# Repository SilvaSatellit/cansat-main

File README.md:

# Team Silva-Satellit

## Informationen

In diesem Respository ist der Sourcecode des Haupt-Mikrocontrollers, der im CanSat verbaut ist, zu finden. Dieser Controller ist für das Auslesen der Temperatur, Luftdruck, Luftfeutigkeit und Gyrodaten verantwortlich.

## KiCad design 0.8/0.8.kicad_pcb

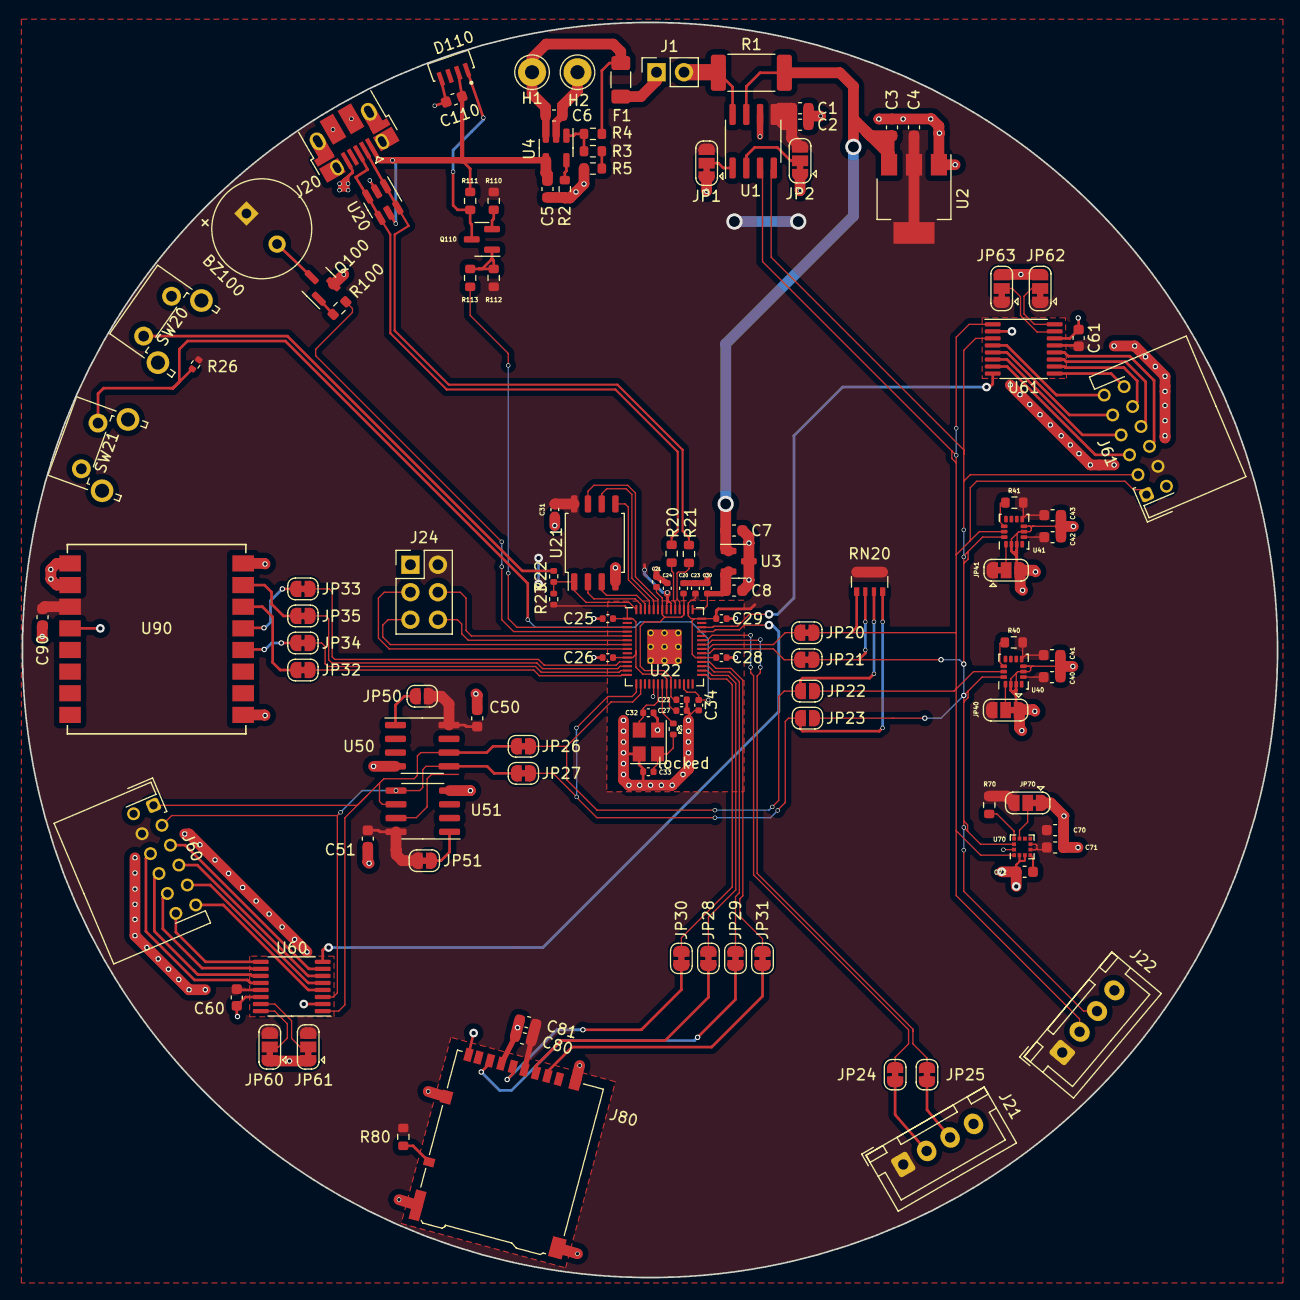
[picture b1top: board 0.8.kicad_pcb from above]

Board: 2 copper layers, 116.0 x 116.0 mm, 119 parts (0 on the bottom side), 98 nets.

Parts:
BZ100: CST-931RP-A; MagneticBuzzer_CUI_CST-931RP-A
C1, C40, C41, C42, C43, C50, C51, C60, C61, C71, C72, C80, C110: 100nF; C_0603_1608Metric
C2: 10uF; C_0603_1608Metric
C3, C70, C81: 1uF; C_0603_1608Metric
C4: 4,7uF; C_0603_1608Metric
C5, C6: 4,7 uF; C_0603_1608Metric
C7: 470nF; C_0603_1608Metric
C8: 10uF => Optional; C_0603_1608Metric
C20, C23, C34: 1uF; C_0402_1005Metric
C21, C22, C24, C25, C26, C27, C28, C29, C30, C31: 100nF; C_0402_1005Metric
C32, C33: 30pF; C_0402_1005Metric
C90: DNP; C_0603_1608Metric
D110: WS2812B-4020; LED_WS2812B-4020
F1: 1.5A; R_1206_3216Metric_Pad1.30x1.75mm_HandSolder
H1: Bat+; Pin_D1.3mm_L11.0mm
H2: Bat-; Pin_D1.3mm_L11.0mm
J1: Switch; PinSocket_1x02_P2.54mm_Vertical
J20: USB_B_Micro; USB_Micro-B_Amphenol_10103594-0001LF_Horizontal
J21: UART; JST_XH_B4B-XH-A_1x04_P2.50mm_Vertical
J22: I2C_01; JST_XH_B4B-XH-A_1x04_P2.50mm_Vertical
J24: GPIO Interface; PinHeader_2x03_P2.54mm_Vertical
J60: Ausenplatine01; JST_PHD_S12B-PHDSS_2x06_P2.00mm_Horizontal
J61: Ausenplatine02; JST_PHD_S12B-PHDSS_2x06_P2.00mm_Horizontal
J80: DM3AT-SF-PEJM5; microSD_HC_Hirose_DM3AT-SF-PEJM5
JP1, JP2, JP40, JP41, JP60, JP61, JP62, JP63, JP70: I2C Adress; SolderJumper-3_P1.3mm_Bridged12_RoundedPad1.0x1.5mm
JP20, JP21, JP24, JP25, JP26, JP27, JP28, JP29, JP30, JP31, JP32, JP33, JP34, JP35: Safety; SolderJumper-2_P1.3mm_Bridged_RoundedPad1.0x1.5mm
JP22: I2C_Master_SCL; SolderJumper-2_P1.3mm_Open_RoundedPad1.0x1.5mm
JP23: I2C_Master_SDA; SolderJumper-2_P1.3mm_Open_RoundedPad1.0x1.5mm
JP50: I2C Adress; SolderJumper-2_P1.3mm_Open_RoundedPad1.0x1.5mm
JP51: I2C Adress; SolderJumper-2_P1.3mm_Bridged_RoundedPad1.0x1.5mm
Q100: MMBT5551L; SOT-23
Q110: S8050; SOT-23
R1: 0.1 R; R_2512_6332Metric_Pad1.40x3.35mm_HandSolder
R2, R5: 2k R; R_0603_1608Metric
R3: 1k R; R_0603_1608Metric
R4, R40, R41, R70: 10k R; R_0603_1608Metric
R20, R21: 27 R; R_0603_1608Metric
R22, R25: 1k R; R_0402_1005Metric
R23: DNP; R_0402_1005Metric
R26: 10k R; R_0402_1005Metric
R80: 100k R; R_0603_1608Metric
R100: 180 R; R_0603_1608Metric
R110, R111, R112: 4.7k R; R_0603_1608Metric
R113: 0 R; R_0603_1608Metric
RN20: 10k R; R_Array_Convex_4x0603
SW20, SW21: Reset; SW_Tactile_SPST_Angled_PTS645Vx39-2LFS
U1: INA219AxD; SOIC-8_3.9x4.9mm_P1.27mm
U2: LDL1117-3.3; SOT-223-3_TabPin2
U3: REF3033; SOT-23
U4: MCP73831-2-OT; SOT-23-5
U20: SRV05-4; SOT-23-6
U21: W25Q128JVS; SOIC-8_5.23x5.23mm_P1.27mm
U22: RP2040; RP2040-QFN-56
U40, U41: LSM6DS3; LGA-14_3x2.5mm_P0.5mm_LayoutBorder3x4y
U50, U51: CAT24C256; SOIC-8_3.9x4.9mm_P1.27mm
U60, U61: ADG728; TSSOP-16_4.4x5mm_P0.65mm
U70: LIS3MDL; LGA-12_2x2mm_P0.5mm
U90: Ai-Thinker-Ra-02; Ai-Thinker-Ra-01-LoRa
locked: 12Mhz; Crystal_SMD_3225-4Pin_3.2x2.5mm

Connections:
+1V1: C20.1, C21.1, C22.1, U22.23 (DVDD), U22.45 (VREG_VOUT), U22.50 (DVDD)
+3.3V: BZ100.1 (-), C1.1, C2.1, C4.1, C23.1, C24.1, C25.1, C26.1, C27.1, C28.1, C29.1, C31.2, C40.2, C41.1, C42.2, C43.1, C50.2, C51.2, C60.2, C61.2, C70.1, C71.1, C80.1, C81.1, C90.1, J21.1, J22.1, J24.2, J60.4, J61.4, J80.4 (VDD), JP1.3 (B), JP2.3 (B), JP40.3 (B), JP41.1 (A), JP50.1 (A), JP51.1 (A), JP60.3 (B), JP61.3 (B), JP62.1 (A), JP63.1 (A), JP70.3 (B), R23.1, R26.2, R40.1, R41.1, R70.1, R80.1, R110.2, R112.2, RN20.1 (R1.1), RN20.2 (R2.1), RN20.3 (R3.1), RN20.4 (R4.1), U1.5 (VS), U2.2 (VO), U21.8 (VCC), U22.1 (IOVDD), U22.10 (IOVDD), U22.22 (IOVDD), U22.33 (IOVDD), U22.42 (IOVDD), U22.44 (VREG_IN), U22.48 (USB_VDD), U22.49 (IOVDD), U40.5 (VDDIO), U40.8 (VDD), U41.5 (VDDIO), U41.8 (VDD), U50.8 (VCC), U51.8 (VCC), U60.13 (VDD), U61.13 (VDD), U70.5 (Vdd), U70.6 (Vdd_IO), U90.3 (VDD)
+3.3VADC: C8.2, C30.2, U3.2 (OUT), U22.43 (ADC_AVDD)
+5V: C5.2, C110.2, D110.2 (VDD), J20.1 (VBUS), R111.2, U4.4 (V_{DD}), U20.5 (VP)
/D+: J20.3 (D+), R20.1, R20.2, U20.3 (IO2), U20.4 (IO3), U22.47 (USB_DP)
/D-: J20.2 (D-), R21.1, R21.2, U20.1 (IO1), U20.6 (IO4), U22.46 (USB_DM)
ADC_01: U22.38 (GPIO26_ADC0), U22.39 (GPIO27_ADC1), U60.8 (D)
ADC_02: U22.40 (GPIO28_ADC2), U22.41 (GPIO29_ADC3), U61.8 (D)
Bat+: C6.1, F1.1, H1.1, R4.1, U4.3 (V_{BAT})
Bat-: C1.2, C2.2, C3.2, C4.2, C5.1, C6.2, C7.1, C8.1, C20.2, C21.2, C22.2, C23.2, C24.2, C25.2, C26.2, C27.2, C28.2, C29.2, C30.1, C31.1, C32.1, C33.2, C34.2, C40.1, C41.2, C42.1, C43.2, C50.1, C51.1, C60.1, C61.1, C70.2, C71.2, C72.2, C80.2, C81.2, C90.2, C110.1, D110.4 (VSS), H2.1, J20.5 (GND), J20.6 (Shield), J21.4, J22.4, J24.1, J60.2, J61.2, J80.6 (VSS), J80.9 (DET_B), J80.11 (SHIELD), JP1.1 (A), JP2.1 (A), JP40.1 (A), JP41.3 (B), JP60.1 (A), JP61.1 (A), JP62.3 (B), JP63.3 (B), JP70.1 (A), Q100.2 (E), R2.2, R5.2, SW20.2, SW21.1, U1.6 (GND), U2.1 (GND), U3.3 (GND), U4.2 (V_{SS}), U20.2 (VN), U21.4 (GND), U22.19 (TESTEN), U22.57 (GND), U40.2 (SDX), U40.3 (SCX), U40.6 (GND), U40.7 (GND), U41.2 (SDX), U41.3 (SCX), U41.6 (GND), U41.7 (GND), U50.4 (GND), U51.4 (GND), U60.14 (GND), U61.14 (GND), U70.2 (GND), U70.3 (GND), U70.12 (GND), U90.1 (GND), U90.2 (GND), U90.9 (GND), U90.16 (GND), locked.2, locked.4
Bat_Charge: R3.2, R5.1
Buzzer_IN: R100.2, U22.4 (GPIO2)
CS_01: J80.2 (DAT3/CD), JP31.1 (A)
CS_02: JP35.1 (A), U90.15 (~NSS)
CS_SPI_01: JP31.2 (B), U22.32 (GPIO21)
CS_SPI_02: JP35.2 (B), U22.12 (GPIO9)
Led_IN: R113.2, U22.3 (GPIO1)
MISO_01: J80.7 (DAT0), JP29.1 (A)
MISO_02: JP33.1 (A), U90.13 (MISO)
MOSI_01: J80.3 (CMD), JP28.1 (A)
MOSI_02: JP32.1 (A), U90.14 (MOSI)
unnamed: BZ100.2 (+), Q100.3 (C)
unnamed: C33.1, R25.1, locked.1
unnamed: D110.1 (DIN), Q110.3 (C), R111.1
unnamed: F1.2, J1.1
unnamed: J1.2, R1.1, U1.8 (IN+)
unnamed: J21.2, JP24.1 (A)
unnamed: J21.3, JP25.1 (A)
unnamed: J24.3, U22.8 (GPIO6)
unnamed: J24.4, U22.5 (GPIO3)
unnamed: J24.5, U22.7 (GPIO5)
unnamed: J24.6, U22.6 (GPIO4)
unnamed: J60.5, U60.7 (S4)
unnamed: J60.6, U60.12 (S5)
unnamed: J60.7, U60.6 (S3)
unnamed: J60.8, U60.11 (S6)
unnamed: J60.9, U60.5 (S2)
unnamed: J60.10, U60.10 (S7)
unnamed: J60.11, U60.4 (S1)
unnamed: J60.12, U60.9 (S8)
unnamed: J61.5, U61.7 (S4)
unnamed: J61.6, U61.12 (S5)
unnamed: J61.7, U61.6 (S3)
unnamed: J61.8, U61.11 (S6)
unnamed: J61.9, U61.5 (S2)
unnamed: J61.10, U61.10 (S7)
unnamed: J61.11, U61.4 (S1)
unnamed: J61.12, U61.9 (S8)
unnamed: JP1.2 (C), U1.1 (A1)
unnamed: JP2.2 (C), U1.2 (A0)
unnamed: JP40.2 (C), U40.1 (SDO/SA0)
unnamed: JP41.2 (C), U41.1 (SDO/SA0)
unnamed: JP50.2 (B), U50.1 (A0)
unnamed: JP51.2 (B), U51.1 (A0)
unnamed: JP60.2 (C), U60.16 (A0)
unnamed: JP61.2 (C), U60.15 (A1)
unnamed: JP62.2 (C), U61.16 (A0)
unnamed: JP63.2 (C), U61.15 (A1)
unnamed: JP70.2 (C), U70.9 (SDO/SA1)
unnamed: Q100.1 (B), R100.1
unnamed: Q110.2 (B), R110.1
unnamed: Q110.1 (E), R112.1, R113.1
unnamed: R22.1, SW20.1
unnamed: C3.1, C7.2, R1.2, U1.7 (IN-), U2.3 (VI), U3.1 (IN)
unnamed: R2.1, U4.5 (PROG)
unnamed: R3.1, R4.2, U4.1 (STAT)
unnamed: U21.6 (CLK), U22.52 (QSPI_SCLK)
unnamed: U21.5 (DI(IO0)), U22.53 (QSPI_SD0)
unnamed: U21.2 (DO(IO1)), U22.55 (QSPI_SD1)
unnamed: U21.3 (IO2), U22.54 (QSPI_SD2)
unnamed: U21.7 (IO3), U22.51 (QSPI_SD3)
unnamed: R22.2, R23.2, U21.1 (~CS), U22.56 (QSPI_SS)
unnamed: C34.1, R26.1, SW21.2, U22.26 (RUN)
unnamed: C32.2, U22.20 (XIN), locked.3
unnamed: R25.2, U22.21 (XOUT)
unnamed: R40.2, U40.12 (CS)
unnamed: R41.2, U41.12 (CS)
unnamed: C72.1, U70.4 (C1)
unnamed: R70.2, U70.10 (~CS)
RX_SPI_01: JP29.2 (B), U22.31 (GPIO20)
RX_SPI_02: JP33.2 (B), U22.11 (GPIO8)
RX_UART_01: JP24.2 (B), U22.37 (GPIO25)
SCK_01: J80.5 (CLK), JP30.1 (A)
SCK_02: JP34.1 (A), U90.12 (SCK)
SCK_SPI_01: JP30.2 (B), U22.29 (GPIO18)
SCK_SPI_02: JP34.2 (B), U22.13 (GPIO10)
SCL_01: J22.2, J61.1, JP20.1 (A), JP22.2 (B), RN20.5 (R4.2), U1.3 (SDA), U40.13 (SCL), U41.13 (SCL), U61.1 (SCL), U70.1 (SCL/SPC)
SCL_03: J60.1, JP26.1 (A), U50.6 (SCL), U51.6 (SCL), U60.1 (SCL)
SCL_Master_01: JP20.2 (B), U22.35 (GPIO23)
SCL_Master_02: JP22.1 (A), JP26.2 (B), RN20.7 (R2.2), U22.16 (GPIO13)
SDA_01: J22.3, J61.3, JP21.1 (A), JP23.2 (B), RN20.6 (R3.2), U1.4 (SCL), U40.14 (SDA), U41.14 (SDA), U61.3 (SDA), U70.11 (SDA/SDI/SDO)
SDA_03: J60.3, JP27.1 (A), U50.5 (SDA), U51.5 (SDA), U60.3 (SDA)
SDA_Master_01: JP21.2 (B), U22.34 (GPIO22)
SDA_Master_02: JP23.1 (A), JP27.2 (B), RN20.8 (R1.2), U22.15 (GPIO12)
SD_Card_DET: J80.10 (DET_A), R80.2
TX_SPI_01: JP28.2 (B), U22.30 (GPIO19)
TX_SPI_02: JP32.2 (B), U22.14 (GPIO11)
TX_UART_01: JP25.2 (B), U22.36 (GPIO24)

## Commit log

2023-11-26 Added first README
2023-12-03 Create PCB-Design
2023-12-28 Update README.md
    Anyone wrote Main Microcontroller instead of our team name
    => Changed that
